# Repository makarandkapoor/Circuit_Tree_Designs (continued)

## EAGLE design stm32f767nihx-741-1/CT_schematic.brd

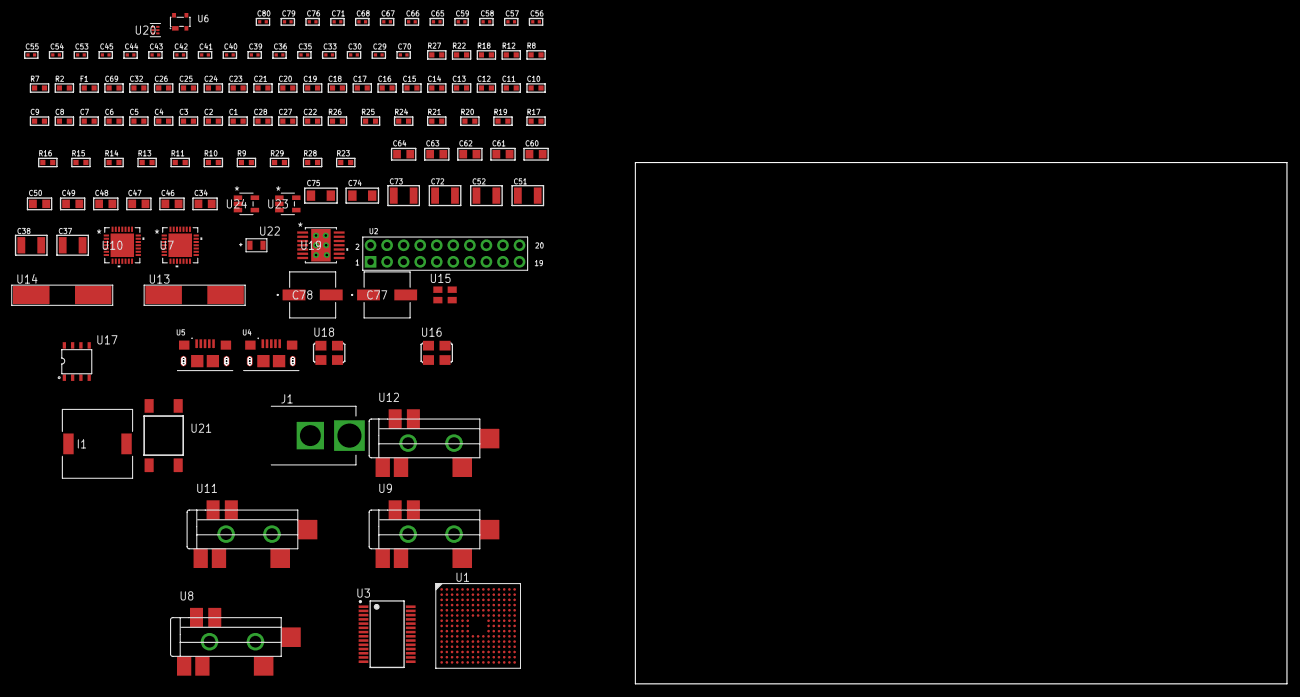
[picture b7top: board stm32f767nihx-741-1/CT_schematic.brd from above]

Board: 2 copper layers, 130 parts (0 on the bottom side), 70 nets, no tracks yet.

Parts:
C1, C25, C32, C69: 1e-06; C0603
C2, C3, C4, C5, C6, C7, C8, C9, C10, C11, C12, C13, C14, C15, C16, C17, C18, C19, C20, C21, C23, C26: 1e-07; C0603
C22: 4.7e-06; C0603
C24: 1e-08; C0603
C27, C28: 2.2e-06; C0603
C29, C30: 1e-11; C0402
C33, C35, C36, C41, C42, C43, C44, C45, C55, C56, C57, C58, C59, C71, C76: 1e-07; C0402
C34: 4.7e-06; C0805
C37, C38, C51, C52, C72, C73: 2.2e-05; C1210
C39, C40, C53, C54: 1e-09; C0402
C46, C47, C48, C49, C50, C60, C61, C62, C63, C64: 1e-05; C0805
C65, C66, C67, C68, C79, C80: 1e-08; C0402
C70: 3.3e-09; C0402
C74, C75: 1e-05; C1206
C77, C78: 0.0001; EXV-9H
F1: 240.0; L0603
I1: 7e-06; DR1040
J1: PJ-037B; PJ-037B_PACKAGE
R2: 1000.0; R0603
R7, R8, R12: 4700.0; R0603
R9, R10, R11, R13, R14, R25, R26: 10000.0; R0603
R15, R16, R17, R19, R20, R21: 47000.0; R0603
R18, R22: 680.0; R0603
R23: 71007.101651032; R0603
R24: 22000.0; R0603
R27: 9100.0; R0603
R28: 680000.0; R0603
R29: 120000.0; R0603
U1: STM32F767NIH6; TFBGA216
U2: arducam_ov2640; ARDUCAM
U3: FT232RL-REEL; SSOP-28
U4, U5: 10118193-0001LF; FCI_10118193-0001LF
U6: prtr5v0u2ax; SOT143B
U7, U10: WM8731CLSEFL; QFN-28
U8, U9, U11, U12: SJ-43515TS-SMT-TR
U13: ABLS-25.000MHZ-B2F-T
U14: ABLS-12.000MHZ-B4-T
U15: ASEK-32.768KHz-ECST; ASEK
U16: ASFL1-12.288MHZ-EC-T; ASFL1
U17: idt74fct38072; IDT74FCT38072
U18: ASFL1-25MHZ-NCS; ASFL1
U19: tps54325PWP; HTSSOP14
U20: TPS3895ADRYR; SON-6
U21: 4-1437565-2; SW_4-1437565-2
U22: Q65110A2395; LGM67K-G1J2-24-Z
U23, U24: nc7sz125m5x; NC7SZ125M5X

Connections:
CLK_CRYSTAL_U1_G1: C29.1, U1.G1, U13.1
CLK_CRYSTAL_U1_H1: C30.1, U1.H1, U13.2
CLK_CRYSTAL_U3_27: U3.27, U14.1
CLK_CRYSTAL_U3_28: U3.28, U14.2
CLK_U1_E1: U1.E1, U15.3
CLK_U2_8: U2.8, U18.3
CLK_U7_1: U7.1, U17.7
CLK_U10_1: U10.1, U17.6
CLK_U17_3: U16.3, U17.3
GND: C1.2, C2.2, C3.2, C4.2, C5.2, C6.2, C7.2, C8.2, C9.2, C10.2, C11.2, C12.2, C13.2, C14.2, C15.2, C16.2, C17.2, C18.2, C19.2, C20.2, C21.2, C22.2, C23.2, C24.2, C25.2, C26.2, C27.2, C28.2, C29.2, C30.2, C32.2, C33.2, C34.2, C35.2, C36.2, C40.2, C41.2, C42.2, C43.2, C44.2, C45.2, C46.2, C47.2, C48.2, C49.2, C50.2, C54.2, C55.2, C56.2, C57.2, C58.2, C59.2, C60.2, C61.2, C62.2, C63.2, C64.2, C65.2, C66.2, C67.2, C68.2, C69.2, C70.2, C72.2, C73.2, C74.2, C75.2, C76.2, C77.2, C78.2, C79.2, C80.2, J1.2, R2.2, R9.2, R11.2, R14.2, R15.2, R16.2, R17.2, R19.2, R20.2, R21.2, R24.2, R27.2, R29.2, U1.F2, U1.F6, U1.F7, U1.F8, U1.F9, U1.F10, U1.G6, U1.G10, U1.H6, U1.H10, U1.J6, U1.J10, U1.K6, U1.K7, U1.K8, U1.K9, U1.K10, U1.L6, U1.M1, U1.N1, U2.2, U2.20, U3.7, U3.18, U3.21, U3.25, U3.26, U4.5, U4.6, U4.7, U4.8, U4.9, U5.5, U5.6, U5.7, U5.8, U5.9, U6.1, U7.4, U7.15, U7.19, U7.25, U7.26, U7.29, U8.1, U9.1, U10.4, U10.15, U10.19, U10.25, U10.26, U10.29, U11.1, U12.1, U15.2, U16.2, U17.4, U17.5, U17.8, U18.2, U19.5, U19.8, U19.9, U19.15, U20.2, U22.C, U23.1, U23.3, U24.1, U24.3
NET_U1_E5: R10.1, U1.E5
NET_U1_E6: R9.1, U1.E6
NET_U1_E11: C28.1, U1.E11
NET_U1_J1: R7.1, U1.J1, U23.4
NET_U1_L5: R11.1, U1.L5
NET_U1_L11: C27.1, U1.L11
NET_U1_R1: C24.1, C25.1, F1.1, U1.P1, U1.R1
NET_U1_R15: U21.3, U21.4
NET_U2_19: R8.1, U2.19, U24.4
NET_U3_14: R13.1, U3.14
NET_U3_17: C35.1, U3.17
NET_U3_19: R14.1, U3.19
NET_U4_1: R12.1, U4.1
NET_U4_2: U3.16, U4.2
NET_U4_3: U3.15, U4.3
NET_U7_20: C45.1, C50.1, U7.20
NET_U8_2: C38.1, R16.1, U8.2
NET_U8_5: C37.1, R15.1, U8.5
NET_U9_5: C39.1, C40.1, R17.1, R18.1, U9.5
NET_U10_20: C59.1, C64.1, U10.20
NET_U11_2: C52.1, R20.1, U11.2
NET_U11_5: C51.1, R19.1, U11.5
NET_U12_5: C53.1, C54.1, R21.1, R22.1, U12.5
NET_U19_2: R23.2, R24.1, U19.2
NET_U19_3: C69.1, U19.3
NET_U19_4: C70.1, U19.4
NET_U19_10: C71.1, I1.1, U19.10, U19.11
NET_U19_12: C71.2, U19.12
NET_U20_1: R26.1, R27.1, U20.1
NET_U20_3: R28.2, R29.1, U20.3
NET_U20_4: R25.1, U20.4, U23.2, U24.2
NET_U21_1: R2.1, U21.1, U21.2
PROC_DCMI_D0: U1.H15, U2.18
PROC_DCMI_D1: U1.D15, U2.17
PROC_DCMI_D2: U1.A6, U2.16
PROC_DCMI_D3: U1.A5, U2.15
PROC_DCMI_D4: U1.A1, U2.14
PROC_DCMI_D5: U1.B6, U2.13
PROC_DCMI_D6: U1.A7, U2.12
PROC_DCMI_D7: U1.B2, U2.11
PROC_DCMI_D8: U1.B14, U2.10
PROC_DCMI_D9: U1.A12, U2.9
PROC_DCMI_HSYNC: U1.N4, U2.6
PROC_DCMI_PIXCLK: U1.P3, U2.7
PROC_DCMI_VSYNC: U1.B5, U2.5
PROC_I2S1_CK: U1.A10, U7.7
PROC_I2S1_SD: U1.A8, U7.8
PROC_I2S1_WS: U1.C8, U7.9, U7.11
PROC_I2S2_CK: U1.C11, U10.7
PROC_I2S2_SD: U1.C13, U10.8
PROC_I2S2_WS: U1.A9, U10.9, U10.11
PROC_UART4_CTS: U1.R5, U3.3
PROC_UART4_RTS: U1.A13, U3.11
PROC_UART4_RX: U1.B12, U3.1
PROC_UART4_TX: U1.C12, U3.5
PROC_USB_OTG_FS_DM: U5.2, U6.3
PROC_USB_OTG_FS_DP: U5.3, U6.2
PROC_USB_OTG_FS_VBUS: U5.1, U6.4
VCC_S1_14V8: C74.1, C75.1, C77.1, C78.1, J1.1, U19.7, U19.13, U19.14
VCC_TIER1_3V3: C1.1, C2.1, C3.1, C4.1, C5.1, C6.1, C7.1, C8.1, C9.1, C10.1, C11.1, C12.1, C13.1, C14.1, C15.1, C16.1, C17.1, C18.1, C19.1, C20.1, C21.1, C22.1, C23.1, C26.1, C32.1, C33.1, C34.1, C36.1, C41.1, C42.1, C43.1, C44.1, C46.1, C47.1, C48.1, C49.1, C55.1, C56.1, C57.1, C58.1, C60.1, C61.1, C62.1, C63.1, C65.1, C66.1, C67.1, C68.1, C72.1, C73.1, C76.1, C79.1, C80.1, F1.2, I1.2, R7.2, R8.2, R10.2, R13.2, R23.1, R25.2, R26.2, R28.1, U1.C1, U1.E7, U1.E8, U1.E9, U1.E10, U1.F4, U1.F5, U1.F11, U1.G5, U1.G11, U1.H5, U1.H11, U1.J5, U1.J11, U1.K5, U1.K11, U1.L7, U1.L8, U1.L9, U1.L10, U2.1, U3.4, U3.20, U7.3, U7.5, U7.12, U7.18, U10.3, U10.5, U10.12, U10.18, U15.4, U16.4, U17.1, U17.2, U18.4, U19.1, U20.6, U23.5, U24.5

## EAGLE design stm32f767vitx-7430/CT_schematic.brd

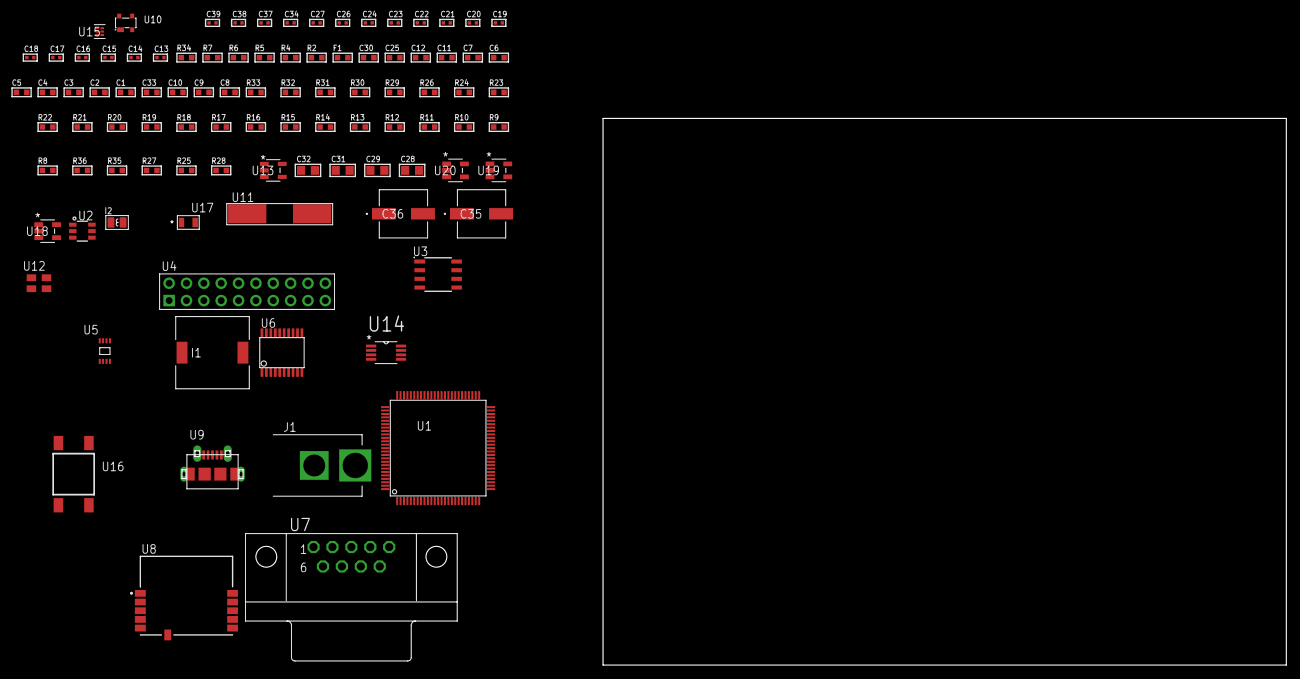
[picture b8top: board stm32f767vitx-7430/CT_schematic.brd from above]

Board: 2 copper layers, 97 parts (0 on the bottom side), 68 nets, no tracks yet.

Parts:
C1, C12, C25, C30: 1e-06; C0603
C2, C3, C4, C5, C6, C7: 1e-07; C0603
C8: 4.7e-06; C0603
C9, C10: 2.2e-06; C0603
C11: 1e-08; C0603
C13, C14: 1e-11; C0402
C15, C18, C27, C37, C38, C39: 1e-08; C0402
C16, C17, C19, C20, C21, C22, C23, C24, C26, C34: 1e-07; C0402
C28, C29, C31, C32: 1e-05; C0805
C33: 1.6e-09; C0603
C35, C36: 0.0001; EXV-9H
F1: 240.0; L0603
I1: 5.2e-06; DR1040
I2: 3.3e-06; L0806
J1: PJ-037B; PJ-037B_PACKAGE
R2: 1000.0; R0603
R4, R5: 4700.0; R0603
R6, R7: 2200.0; R0603
R8, R26, R29: 47000.0; R0603
R9, R10, R11, R12, R13, R14, R15, R16, R17, R18, R19, R20, R21, R22, R23, R24, R32, R33: 10000.0; R0603
R25: 100000.0; R0603
R27: 220000.0; R0603
R28: 1000000.0; R0603
R30: 56000.0; R0603
R31: 18000.0; R0603
R34: 9100.0; R0603
R35: 680000.0; R0603
R36: 120000.0; R0603
U1: STM32F767VIT6; LQFP100
U2: MAX4995AAUT+T; SOT-23-6
U3: AT25020B-SSHL-T; SOIC-8
U4: TST-110-05-T-D-RA
U5: 24AA64T-I/MNY; TDFN-8/6MM
U6: SP3203ECY-L/TR; TSSOP20-I
U7: 182-009-113R531; 182-009-MALE
U8: SPBTLE-RF; XCVR_SPBTLE-RF
U9: 47590-0001; MICRO_USB_AB
U10: prtr5v0u2ax; SOT143B
U11: ABLS-25.000MHZ-B2F-T
U12: ASEK-32.768KHz-ECST; ASEK
U13: ltc3406es5; TSOT-23-5
U14: TPS61085DGKR; MSOP-8
U15: TPS3895ADRYR; SON-6
U16: 4-1437565-2; SW_4-1437565-2
U17: Q65110A2395; LGM67K-G1J2-24-Z
U18, U19, U20: nc7sz125m5x; NC7SZ125M5X

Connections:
CLK_CRYSTAL_U1_12: C13.1, U1.12, U11.1
CLK_CRYSTAL_U1_13: C14.1, U1.13, U11.2
CLK_U1_8: U1.8, U12.3
GND: C1.2, C2.2, C3.2, C4.2, C5.2, C6.2, C7.2, C8.2, C9.2, C10.2, C11.2, C12.2, C13.2, C14.2, C15.2, C16.2, C17.2, C18.2, C19.2, C20.2, C23.2, C24.2, C25.2, C26.2, C27.2, C28.2, C29.1, C29.2, C30.2, C31.2, C32.1, C32.2, C33.1, C33.2, C34.2, C35.2, C36.2, C37.2, C38.2, C39.2, J1.2, R2.2, R8.2, R9.2, R11.2, R20.2, R23.2, R25.2, R26.2, R27.2, R31.2, R34.2, R36.2, U1.10, U1.19, U1.26, U1.49, U1.74, U1.99, U2.2, U3.4, U4.4, U4.6, U4.8, U4.10, U4.12, U4.14, U4.16, U4.18, U4.20, U5.4, U6.18, U7.5, U8.6, U9.5, U9.6, U9.7, U9.8, U9.9, U10.1, U12.2, U13.2, U14.4, U15.2, U17.C, U18.2, U18.3, U19.1, U19.3, U20.1, U20.3
NET_U1_14: R5.1, U1.14, U20.4
NET_U1_21: C11.1, C12.1, F1.1, U1.20, U1.21
NET_U1_48: C9.1, U1.48
NET_U1_73: C10.1, U1.73
NET_U1_92: R6.1, U1.92, U5.6
NET_U1_93: R7.1, U1.93, U5.5
NET_U1_94: R9.1, U1.94
NET_U1_98: U16.3, U16.4
NET_U2_3: R8.1, U2.3
NET_U3_3: R12.1, U3.3
NET_U3_7: R14.1, U3.7
NET_U4_19: R20.1, U4.19
NET_U5_1: R21.1, U5.1
NET_U5_2: R22.1, U5.2
NET_U5_3: R23.1, U5.3
NET_U6_1: C21.1, U6.1
NET_U6_2: C23.1, U6.2
NET_U6_3: C21.2, U6.3
NET_U6_4: C22.1, U6.4
NET_U6_5: C22.2, U6.5
NET_U6_6: C24.1, U6.6
NET_U7_2: U6.14, U7.2
NET_U7_3: U6.17, U7.3
NET_U7_7: U6.13, U7.7
NET_U7_8: U6.16, U7.8
NET_U8_11: R4.1, U8.11, U19.4
NET_U13_3: I1.1, U13.3
NET_U13_5: R27.1, R28.1, U13.5
NET_U13_ATNET_3: I1.2, R28.2
NET_U14_1: R29.1, U14.1
NET_U14_2: R30.1, R31.1, U14.2
NET_U14_5: I2.1, U14.5
NET_U15_1: R33.1, R34.1, U15.1
NET_U15_3: R35.2, R36.1, U15.3
NET_U15_4: R32.1, U15.4, U18.4, U19.2, U20.2
NET_U16_1: R2.1, U16.1, U16.2
PROC_GPIO_TO_U1_USB_FAULT: R10.1, U1.2, U2.6
PROC_GPIO_TO_U1_VBUS_EN: R11.1, U1.1, U2.4
PROC_GPIO_TO_U8_SPI_IRQ: R26.1, U1.3, U8.4
PROC_SPI1_MISO: U1.30, U8.8
PROC_SPI1_MOSI: U1.31, U8.9
PROC_SPI1_NSS: R24.1, U1.28, U8.10
PROC_SPI1_SCK: R25.1, U1.29, U8.7
PROC_SPI2_MISO: U1.17, U3.2
PROC_SPI2_MOSI: U1.16, U3.5
PROC_SPI2_NSS: R13.1, U1.51, U3.1
PROC_SPI2_SCK: U1.46, U3.6
PROC_SYS_JTCK_SWCLK: R18.1, U1.76, U4.9
PROC_SYS_JTDI: R16.1, U1.77, U4.5
PROC_SYS_JTDO_SWO: U1.89, U4.13
PROC_SYS_JTMS_SWDIO: R17.1, U1.72, U4.7
PROC_SYS_JTRST: R15.1, U1.90, U4.3
PROC_UART4_CTS: U1.34, U6.8
PROC_UART4_RTS: U1.53, U6.10
PROC_UART4_RX: U1.23, U6.11
PROC_UART4_TX: U1.22, U6.7
PROC_USB_OTG_FS_DM: U1.70, U9.2, U10.3
PROC_USB_OTG_FS_DP: U1.71, U9.3, U10.2
PROC_USB_OTG_FS_ID: U1.69, U9.4
PROC_USB_OTG_FS_VBUS: U1.68, U2.1, U9.1, U10.4
RST_OUT_U4_SRESET_B: R19.1, U4.15, U18.1
VCC_S1_4V8: C28.1, C30.1, C31.1, C35.1, C36.1, I2.2, J1.1, U13.4, U14.3, U14.6
VCC_TIER1_3V3: C1.1, C2.1, C3.1, C4.1, C5.1, C6.1, C7.1, C8.1, C15.1, C16.1, C17.1, C18.1, C19.1, C20.1, C25.1, C26.1, C27.1, C29.2, C34.1, C37.1, C38.1, C39.1, F1.2, I1.2, R4.2, R5.2, R6.2, R7.2, R10.2, R12.2, R13.2, R14.2, R15.2, R16.2, R17.2, R18.2, R19.2, R21.2, R22.2, R24.2, R28.2, R32.2, R33.2, R35.1, U1.6, U1.11, U1.27, U1.50, U1.75, U1.100, U3.8, U4.1, U4.2, U5.7, U5.8, U6.12, U6.19, U8.5, U12.4, U15.6, U18.5, U19.5, U20.5
VCC_TIER1_5V0: C32.2, R30.2, U2.5
